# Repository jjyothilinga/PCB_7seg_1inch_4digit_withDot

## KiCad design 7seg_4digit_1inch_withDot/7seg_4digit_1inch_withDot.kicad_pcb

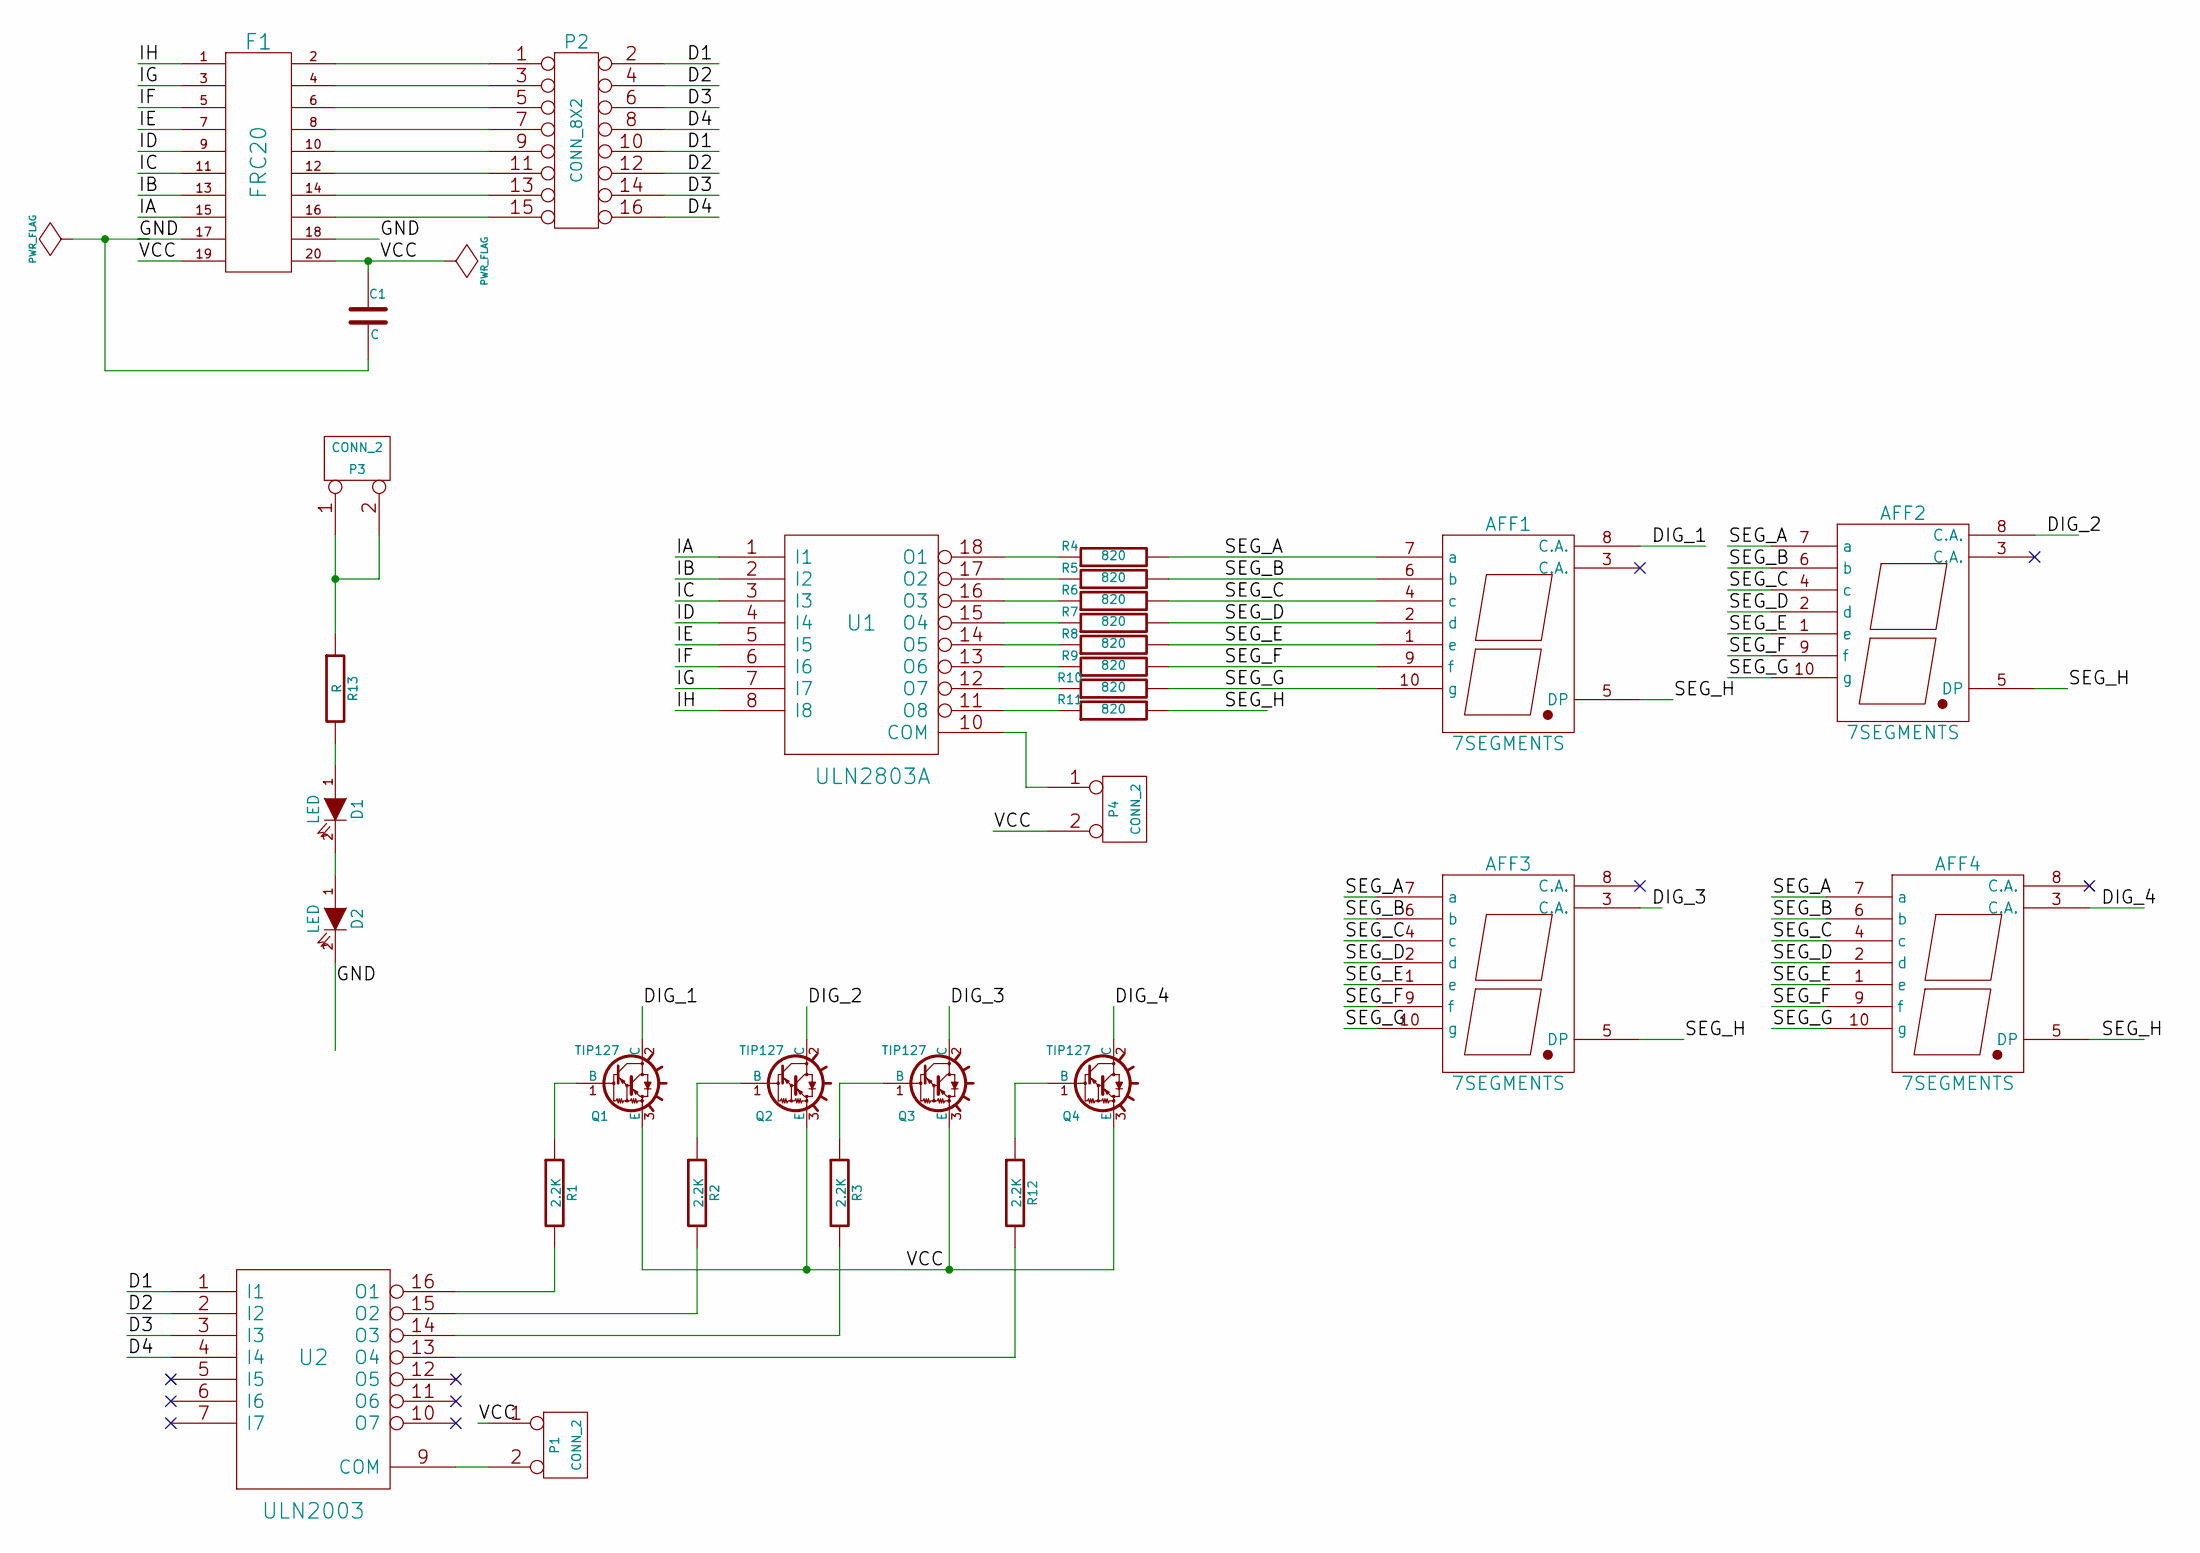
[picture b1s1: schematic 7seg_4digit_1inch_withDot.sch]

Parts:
AFF1, AFF2, AFF3, AFF4: 7SEGMENTS
C1: C
D1, D2: LED
F1: FRC20
P1, P3, P4: CONN_2
P2: CONN_8X2
Q1, Q2, Q3, Q4: TIP127; TO220
R1, R2, R3, R12: 2.2K
R4, R5, R6, R7, R8, R9, R10, R11: 820
R13: R
U1: ULN2803A
U2: ULN2003

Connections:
/D1: P2.2, P2.10, U2.1 (I1)
/D2: P2.4, P2.12, U2.2 (I2)
/D3: P2.6, P2.14, U2.3 (I3)
/D4: P2.8, P2.16, U2.4 (I4)
/DIG_1: AFF1.8 (C.A.), Q1.2 (C)
/DIG_2: AFF2.8 (C.A.), Q2.2 (C)
/DIG_3: AFF3.3 (C.A.), Q3.2 (C)
/DIG_4: AFF4.3 (C.A.), Q4.2 (C)
/IA: F1.15, U1.1 (I1)
/IB: F1.13, U1.2 (I2)
/IC: F1.11, U1.3 (I3)
/ID: F1.9, U1.4 (I4)
/IE: F1.7, U1.5 (I5)
/IF: F1.5, U1.6 (I6)
/IG: F1.3, U1.7 (I7)
/IH: F1.1, U1.8 (I8)
/SEG_A: AFF1.7 (a), AFF2.7 (a), AFF3.7 (a), AFF4.7 (a), R4.2
/SEG_B: AFF1.6 (b), AFF2.6 (b), AFF3.6 (b), AFF4.6 (b), R5.2
/SEG_C: AFF1.4 (c), AFF2.4 (c), AFF3.4 (c), AFF4.4 (c), R6.2
/SEG_D: AFF1.2 (d), AFF2.2 (d), AFF3.2 (d), AFF4.2 (d), R7.2
/SEG_E: AFF1.1 (e), AFF2.1 (e), AFF3.1 (e), AFF4.1 (e), R8.2
/SEG_F: AFF1.9 (f), AFF2.9 (f), AFF3.9 (f), AFF4.9 (f), R9.2
/SEG_G: AFF1.10 (g), AFF2.10 (g), AFF3.10 (g), AFF4.10 (g), R10.2
/SEG_H: AFF1.5 (DP), AFF2.5 (DP), AFF3.5 (DP), AFF4.5 (DP), R11.2
/VCC: C1.1, F1.19, F1.20, P1.1, P4.2 (PM), Q1.3 (E), Q2.3 (E), Q3.3 (E), Q4.3 (E)
GND: C1.2, D2.2 (K), F1.17, F1.18, U1.9 (GND), U2.8 (GND)
unnamed: R2.2, U2.15 (O2)
unnamed: R1.2, U2.16 (O1)
unnamed: Q2.1 (B), R2.1
unnamed: Q1.1 (B), R1.1
unnamed: R3.2, U2.14 (O3)
unnamed: P1.2 (PM), U2.9 (COM)
unnamed: F1.12, P2.11
unnamed: F1.10, P2.9
unnamed: F1.8, P2.7
unnamed: F1.6, P2.5
unnamed: F1.4, P2.3
unnamed: F1.2, P2.1
unnamed: R12.2, U2.13 (O4)
unnamed: Q4.1 (B), R12.1
unnamed: F1.16, P2.15
unnamed: F1.14, P2.13
unnamed: D1.1 (A), R13.2
unnamed: P3.1, P3.2 (PM), R13.1
unnamed: D1.2 (K), D2.1 (A)
unnamed: R6.1, U1.16 (O3)
unnamed: R11.1, U1.11 (O8)
unnamed: R10.1, U1.12 (O7)
unnamed: R9.1, U1.13 (O6)
unnamed: R8.1, U1.14 (O5)
unnamed: R7.1, U1.15 (O4)
unnamed: R5.1, U1.17 (O2)
unnamed: R4.1, U1.18 (O1)
unnamed: P4.1, U1.10 (COM)
unnamed: Q3.1 (B), R3.1

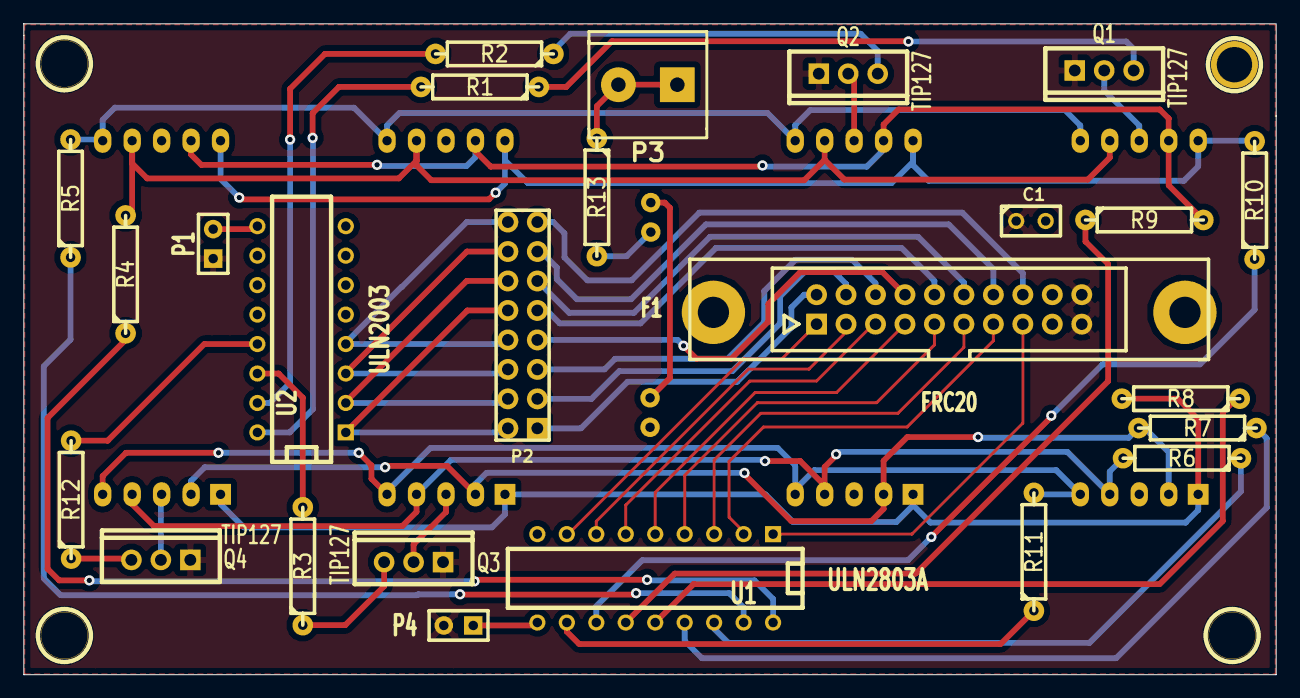
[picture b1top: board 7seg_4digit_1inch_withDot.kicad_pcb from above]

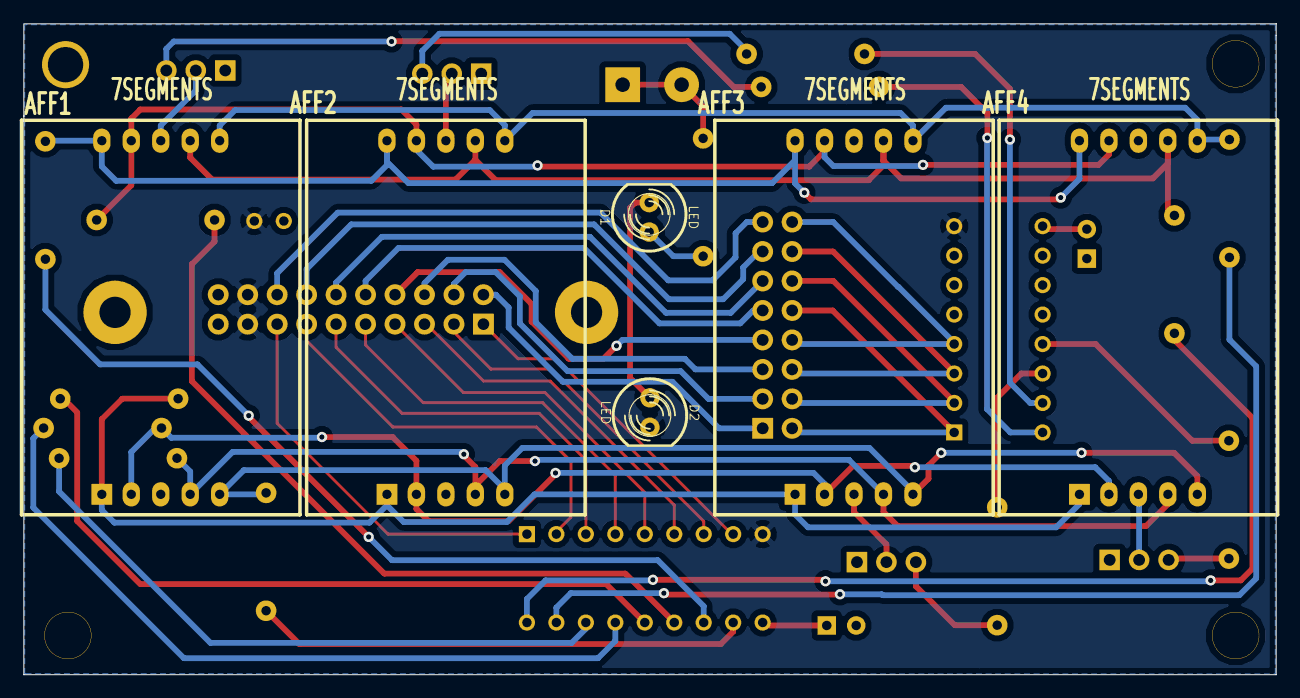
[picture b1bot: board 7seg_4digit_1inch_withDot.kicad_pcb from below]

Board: 2 copper layers, 108.0 x 56.1 mm, 35 parts (6 on the bottom side), 55 nets.

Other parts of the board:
1PIN, 1PIN#2, 1PIN#3, 1PIN#4: P***; 1pin

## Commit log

2015-07-08 :boom::camel: Added .gitattributes & .gitignore files
2015-07-08 Completed
